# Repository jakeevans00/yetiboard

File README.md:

# yetiboard

My first truly custom keyboard. 

## Overview
In this README, I'll walk through my experience on the ergo-keyboard journey. 

First, a little about me though! I'm new to the custom keyboard scene and I don't know how deep I'll eventually go. My aspirations as of now are as follows:
1. Finish one (seriously can't let this be another half-finished project) 

And my specific keyboard goals!
1. 1 key away 
2. Macro-friendly
3. Lok cool

So for now, I've settled on a 38-key design. Taking a lot of ideas from my first ergo keyboard - the Glove80. The only thing I can say for the Glove80 design is that it is excellent. So, for this first stab, I hope to mimic the layout I've been using for the past few months and continue the use of home-row mods, tri-thumb keys, and layers.

### 38-key Design

  q w e r t            y u i o p
` a s d f g            h j k l ; '
  z x c v b            n m , . /
     BK DEL ESC    ENT TAB SPACE

PCB Matrix: (Need 16 Pins)

  C0 C1 C2 C3 C4 C5      C6 C7 C8 C9 C10 C11
R1
R2
R3
R4	

will need exactly 16 pins for this I think

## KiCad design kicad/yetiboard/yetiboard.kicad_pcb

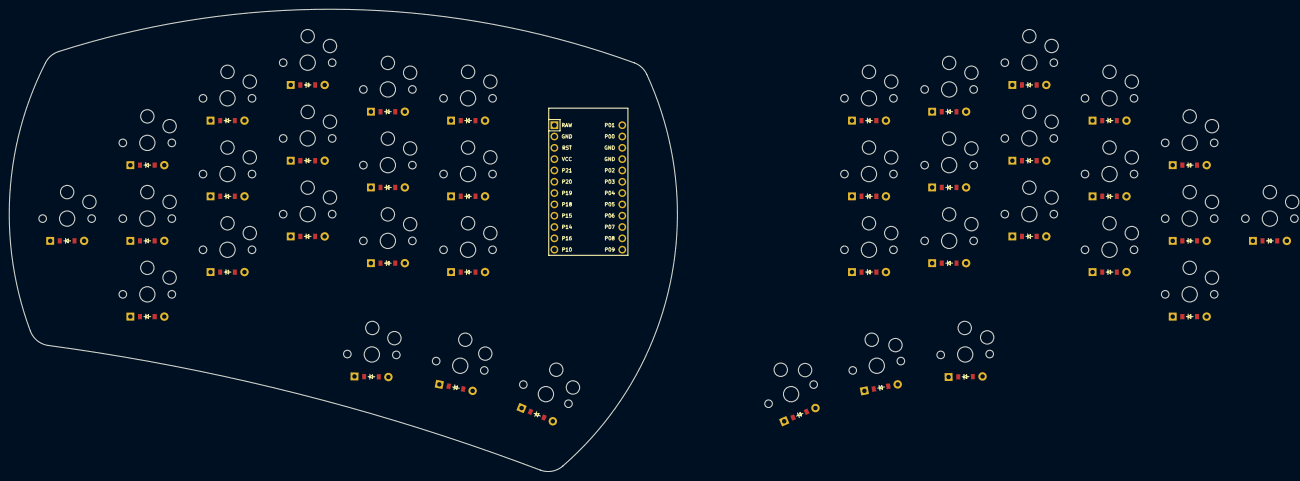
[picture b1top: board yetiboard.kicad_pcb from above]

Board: 2 copper layers, 150.0 x 103.8 mm, 77 parts (0 on the bottom side), 39 nets, no tracks yet.

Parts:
D1, D2, D3, D4, D5, D6, D7, D8, D9, D10, D11, D12, D13, D14, D15, D16, D17, D18, D19, D20, D21, D22, D23, D24, D25, D26, D27, D28, D29, D30, D31, D32, D33, D34, D35, D36, D37, D38: ComboDiode
MCU1: ProMicro
S1, S2, S3, S4, S5, S6, S7, S8, S9, S10, S11, S12, S13, S14, S15, S16, S17, S18, S19, S20, S21, S22, S23, S24, S25, S26, S27, S28, S29, S30, S31, S32, S33, S34, S35, S36, S37, S38: PG1350

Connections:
GND: MCU1.2, MCU1.15, MCU1.16
close_home: D17.2, S17.2
far_home: D19.2, S19.2
index_bottom: D11.2, S11.2
index_home: D12.2, S12.2
index_top: D13.2, S13.2
inner_bottom: D14.2, S14.2
inner_home: D15.2, S15.2
inner_top: D16.2, S16.2
mid_home: D18.2, S18.2
middle_bottom: D8.2, S8.2
middle_home: D9.2, S9.2
middle_top: D10.2, S10.2
mirror_close_home: D36.2, S36.2
mirror_far_home: D38.2, S38.2
mirror_index_bottom: D30.2, S30.2
mirror_index_home: D31.2, S31.2
mirror_index_top: D32.2, S32.2
mirror_inner_bottom: D33.2, S33.2
mirror_inner_home: D34.2, S34.2
mirror_inner_top: D35.2, S35.2
mirror_mid_home: D37.2, S37.2
mirror_middle_bottom: D27.2, S27.2
mirror_middle_home: D28.2, S28.2
mirror_middle_top: D29.2, S29.2
mirror_outer_home: D20.2, S20.2
mirror_pinky_bottom: D21.2, S21.2
mirror_pinky_home: D22.2, S22.2
mirror_pinky_top: D23.2, S23.2
mirror_ring_bottom: D24.2, S24.2
mirror_ring_home: D25.2, S25.2
mirror_ring_top: D26.2, S26.2
outer_home: D1.2, S1.2
pinky_bottom: D2.2, S2.2
pinky_home: D3.2, S3.2
pinky_top: D4.2, S4.2
ring_bottom: D5.2, S5.2
ring_home: D6.2, S6.2
ring_top: D7.2, S7.2

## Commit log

2025-06-08 fix: initial commit
2025-06-12 feat: create layouts v1 and base yaml
2025-06-15 feat: add extra pinky key
2025-06-15 feat: add mirror to keys
2025-06-18 feat: finish points
2025-06-21 feat: outline v1
2025-06-23 feat: final outline
2025-06-29 fix: tweak the outline
2025-06-30 chore: update readme
2025-07-04 chore: useless update
2025-07-07 feat: generate base pcb file
2025-07-19 Add notes on matrix to README
